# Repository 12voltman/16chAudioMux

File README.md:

# 16chAudioMux
4 to 16 Audio mux with low impedance and microcontroller for route switching

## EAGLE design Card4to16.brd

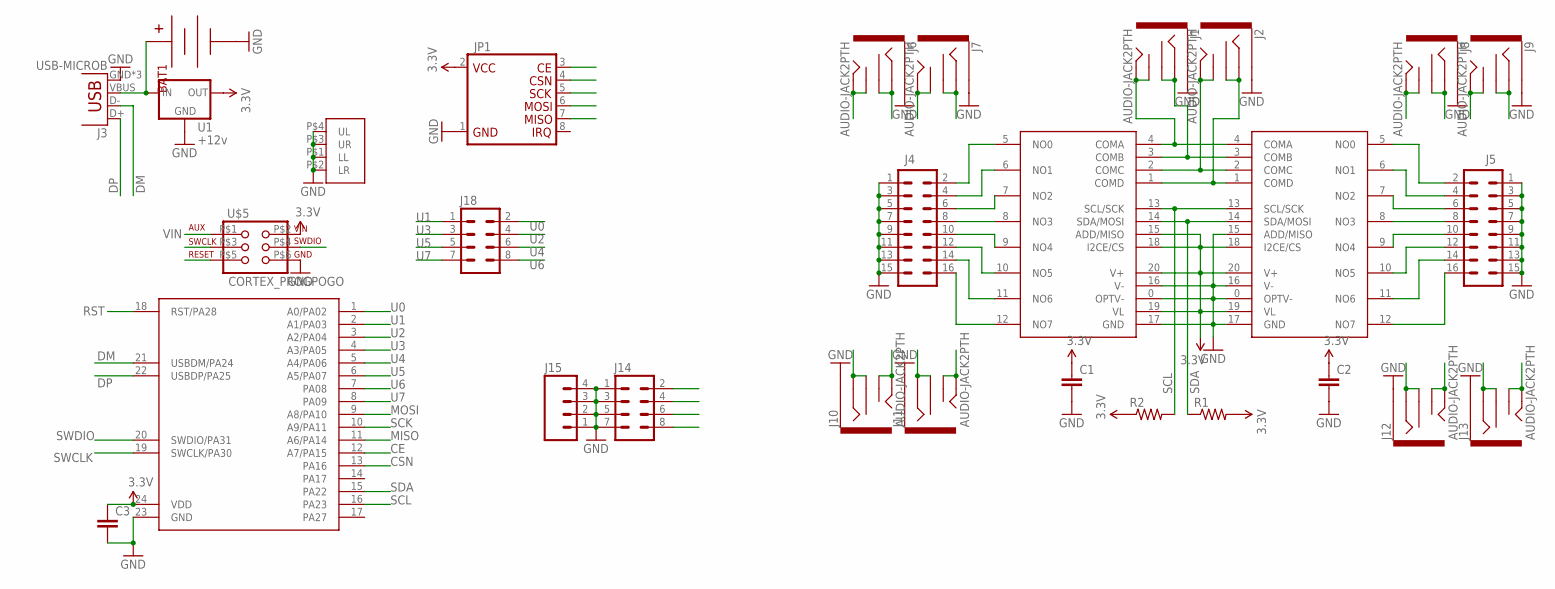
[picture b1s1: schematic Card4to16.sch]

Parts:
BAT1: 9VHOLDERCLIPS; BSPC9V
C1, C2, C3: CAP0805; 0805
J1, J2, J6, J7, J8, J9, J10, J11, J12, J13: AUDIO-JACK2PTH; AUDIO-JACK
J3: USB-MICROB
J4, J5: M08X2; 2X8
J14, J18: M04X2; 2X4
J15: M04PTH; 1X04
JP1: NRF24L01+SHORT_FLUSH; NRF24L01SHORT
R1, R2: RESISTOR0603-RES; 0603-RES
U1: +12v; TO-252
U$1, U$2: MAX14724ETP+QFN; QFN20_4X4
U$3: ATSAMD11D14A-M; QFN24_4X4
U$4: CARD_HOLESHOLES; IEC-7810_ID-1_HOLES
U$5: CORTEX_PROGPOGO; 2X3_MAX

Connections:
3.3V: C1.1, C2.1, C3.1, JP1.2 (VCC), R1.2, R2.1, U1.2 (OUT), U$1.15 (ADD/MISO), U$1.18 (I2CE/CS), U$1.19 (VL), U$1.20 (V+), U$2.18 (I2CE/CS), U$2.19 (VL), U$2.20 (V+), U$3.24 (VDD), U$5.P$2 (VIN)
CE: JP1.3 (CE), U$3.12 (A7/PA15)
COMA: J1.TIP, J1.TSH, J14.2, U$1.4 (COMA), U$2.4 (COMA)
COMB: J1.RING, J1.RSH, J14.4, U$1.3 (COMB), U$2.3 (COMB)
COMC: J2.TIP, J2.TSH, J14.6, U$1.2 (COMC), U$2.2 (COMC)
COMD: J2.RING, J2.RSH, J14.8, U$1.1 (COMD), U$2.1 (COMD)
CSN: JP1.4 (CSN), U$3.13 (PA16)
DM: J3.D-, U$3.21 (USBDM/PA24)
DP: J3.D+, U$3.22 (USBDP/PA25)
GND: BAT1.P$1 (V-), BAT1.P$2 (V-), BAT1.P$3 (V-), C1.2, C2.2, C3.2, J1.SLEEVE, J2.SLEEVE, J3.GND, J3.MT1 (GND), J3.MT2 (GND), J4.1, J4.3, J4.5, J4.7, J4.9, J4.11, J4.13, J4.15, J5.1, J5.3, J5.5, J5.7, J5.9, J5.11, J5.13, J5.15, J6.SLEEVE, J7.SLEEVE, J8.SLEEVE, J9.SLEEVE, J10.SLEEVE, J11.SLEEVE, J12.SLEEVE, J13.SLEEVE, J14.1, J14.3, J14.5, J14.7, J15.1, J15.2, J15.3, J15.4, JP1.1 (GND), U1.3 (GND), U$1.0 (OPTV-), U$1.16 (V-), U$1.17 (GND), U$2.0 (OPTV-), U$2.15 (ADD/MISO), U$2.16 (V-), U$2.17 (GND), U$3.23 (GND), U$4.P$1 (LL), U$4.P$2 (LR), U$4.P$3 (UR), U$4.P$4 (UL), U$5.P$6 (GND)
MISO: JP1.7 (MISO), U$3.11 (A6/PA14)
MOSI: JP1.6 (MOSI), U$3.9 (A8/PA10)
OUT1: J4.2, J10.RING, J10.RSH, U$1.5 (NO0)
OUT2: J4.4, J10.TIP, J10.TSH, U$1.6 (NO1)
OUT3: J4.6, J11.RING, J11.RSH, U$1.7 (NO2)
OUT4: J4.8, J11.TIP, J11.TSH, U$1.8 (NO3)
OUT5: J4.10, J12.RING, J12.RSH, U$1.9 (NO4)
OUT6: J4.12, J12.TIP, J12.TSH, U$1.10 (NO5)
OUT7: J4.14, J13.RING, J13.RSH, U$1.11 (NO6)
OUT8: J4.16, J13.TIP, J13.TSH, U$1.12 (NO7)
OUT9: J5.2, J6.RING, J6.RSH, U$2.5 (NO0)
OUT10: J5.4, J6.TIP, J6.TSH, U$2.6 (NO1)
OUT11: J5.6, J7.RING, J7.RSH, U$2.7 (NO2)
OUT12: J5.8, J7.TIP, J7.TSH, U$2.8 (NO3)
OUT13: J5.10, J8.RING, J8.RSH, U$2.9 (NO4)
OUT14: J5.12, J8.TIP, J8.TSH, U$2.10 (NO5)
OUT15: J5.14, J9.RING, J9.RSH, U$2.11 (NO6)
OUT16: J5.16, J9.TIP, J9.TSH, U$2.12 (NO7)
RST: U$3.18 (RST/PA28), U$5.P$5 (RST)
SCK: JP1.5 (SCK), U$3.10 (A9/PA11)
SCL: R2.2, U$1.13 (SCL/SCK), U$2.13 (SCL/SCK), U$3.16 (PA23)
SDA: R1.1, U$1.14 (SDA/MOSI), U$2.14 (SDA/MOSI), U$3.15 (PA22)
SWCLK: U$3.19 (SWCLK/PA30), U$5.P$3 (SWCLK)
SWDIO: U$3.20 (SWDIO/PA31), U$5.P$4 (SWDIO)
U0: J18.2, U$3.1 (A0/PA02)
U1: J18.1, U$3.2 (A1/PA03)
U2: J18.4, U$3.3 (A2/PA04)
U3: J18.3, U$3.4 (A3/PA05)
U4: J18.6, U$3.5 (A4/PA06)
U5: J18.5, U$3.6 (A5/PA07)
U6: J18.8, U$3.7 (PA08)
U7: J18.7, U$3.8 (PA09)
VIN: BAT1.P$4 (V+), BAT1.P$5 (V+), BAT1.P$6 (V+), J3.VBUS, U1.1 (IN), U$5.P$1 (AUX)

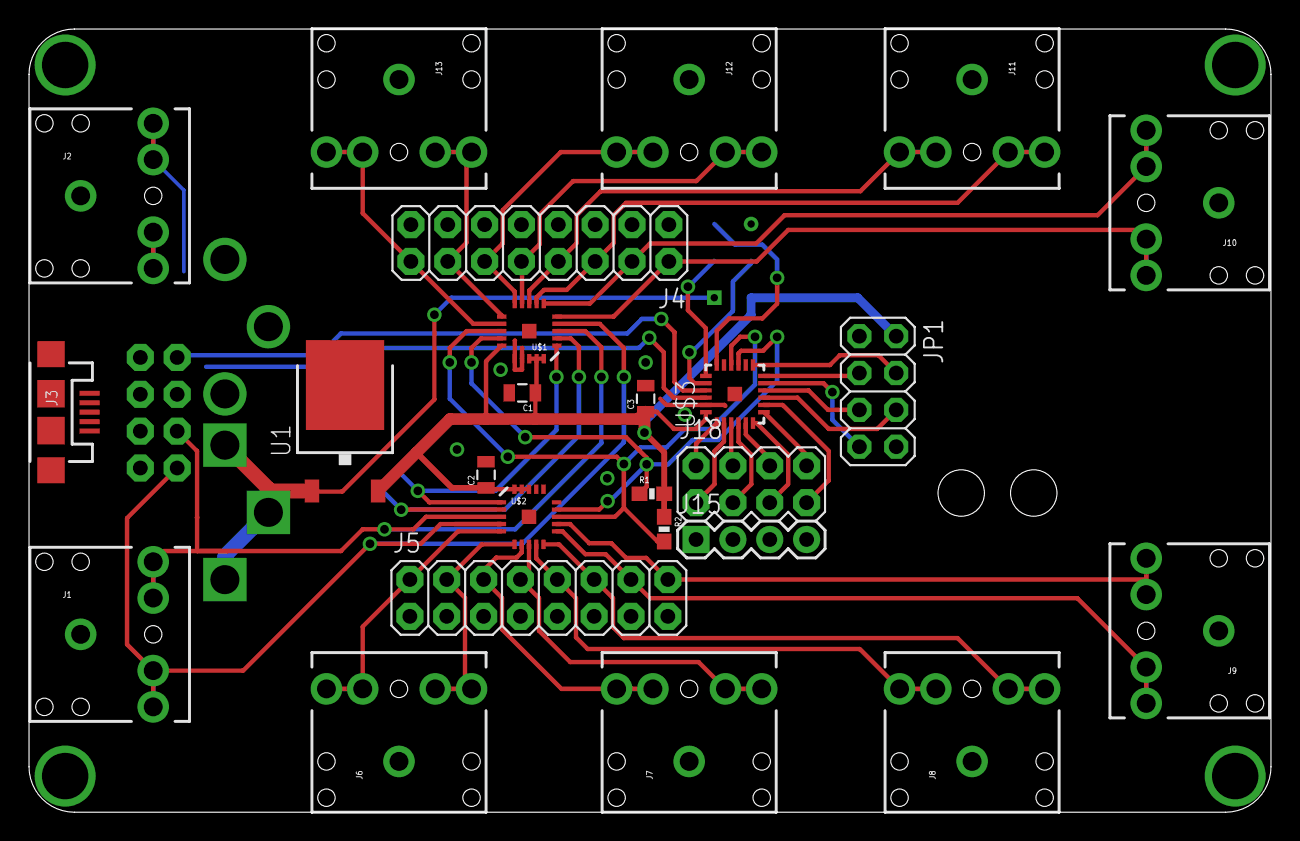
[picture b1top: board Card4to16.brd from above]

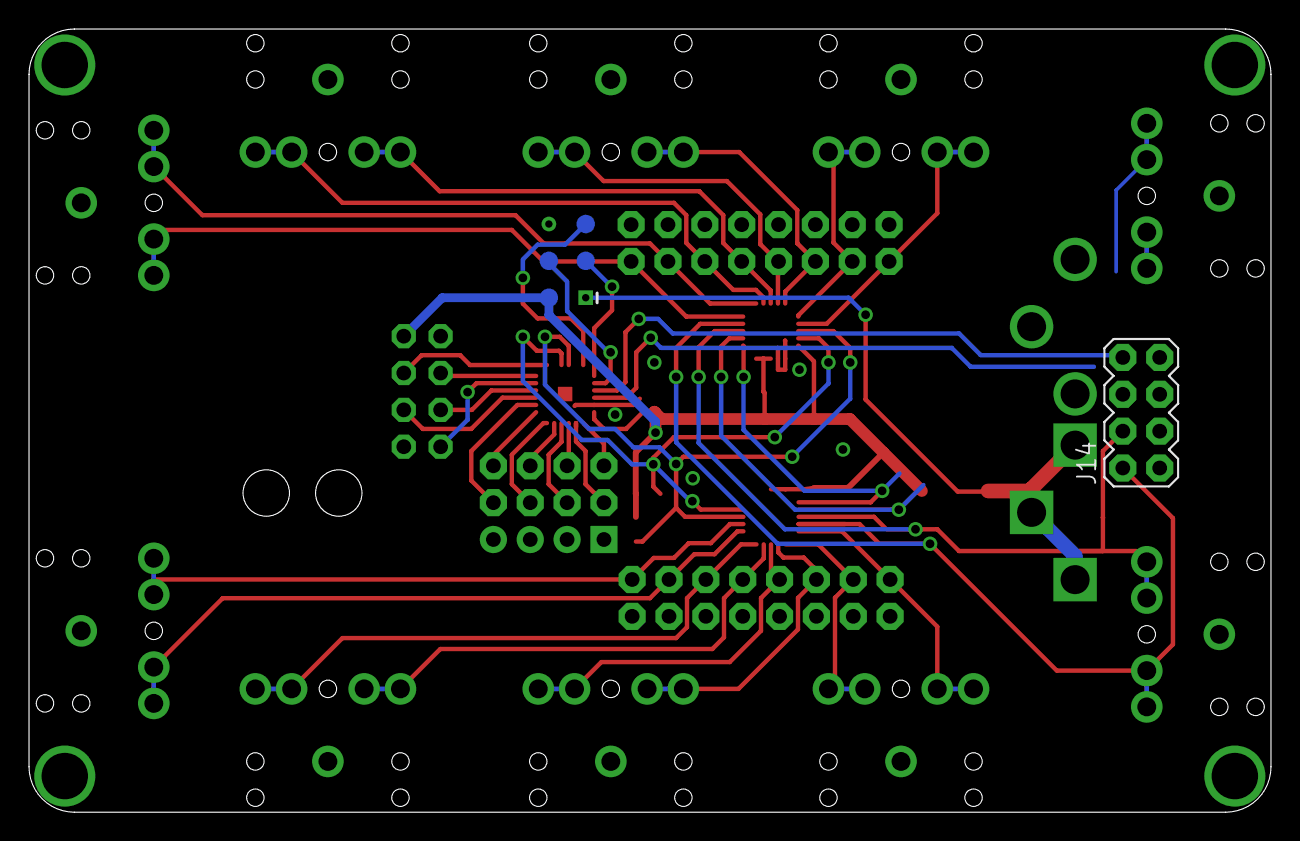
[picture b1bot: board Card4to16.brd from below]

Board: 2 copper layers, 85.6 x 54.0 mm, 29 parts (2 on the bottom side), 43 nets.

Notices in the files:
parts and their libraries:
SparkFun-Connectors: Licensing: Creative Commons ShareAlike 4.0 International - https://creativecommons.org/licenses/by-sa/4.0
